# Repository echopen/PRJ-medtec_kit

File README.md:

# Project

## Name
[`PRJ-medtec_kit`]()

## Title @lang=fr
Projet de kit d'expérimentation

## Title @lang=en
Experiment kit project

## About @lang=en
Designing a modular hardware development kit to spread the project and raise contributions.

## Challenge
[`CHG-medtec`]()

## Uses
This repository provid all is needed to make an echOpen kit. It is divided in six folders:  
+ **configurations**, in this folder one find the different working configuration to have a functional kit. It lists the différent daughter board to plug on a mother and the mecanic modules used.  
+ **electronic**, in this folder one can find the daughter boards sources, plans... And to software for the microcontrolers or FPGA.  
+ **installation**, in this folder one can find the instruction to download and install the software need by your computer (linux or windows user). There is also the instructions for installing boards such as arduino or RedPitaya and how to launch the kit.  
+ **license**, in this folder one can find the echOpen license.  
+ **mecanic**, in this folder one can find the sources for mecanic pieces.  
+ **miscellanous** contain informations about functions and interfaces.

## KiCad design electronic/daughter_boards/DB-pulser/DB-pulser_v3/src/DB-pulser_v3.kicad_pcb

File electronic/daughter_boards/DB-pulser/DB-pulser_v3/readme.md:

# Daughter_board

## Name
[`DB-pulser_v2`]()

## Title
Daughter board pulser version 3

## Author
* [`CTC-dubois_jerome`]()

## Modules included
* [`MDL-pulser_v1`]()

## Interfaces
### Input
* [`ITF-A_gnd`]()
* [`ITF-F_12v`]()
* [`ITF-I_pulse_on`]()

### Output
* [`ITF-A_gnd`]()

##External connections
### Input
* -100V (P2, P6)

### Output
* -100V pulse (P4, P5, P7, P8)

## Scheme

## Remarks
[BOM](./src/DB-pulser_v1.csv)

If the cable connecting the transducer to the pulse is too long, one might have loop effect. This can be avoid with impedance adaptation, we are currently working on that.

-100V input is connected to P2 or P6 (angled socket and SMA connector respectively). Connector P4, P5, P7 and P8 are used to plugged the transducer and to connect with DB-tr_switch_tgc.

A small 47 ohms resistors had to be add to have the pulse, it don't work without it.

## Results

## Pros/Cons/Constraint:

**Pros:** cheap solution

**Cons:** NA

**Constraint:** NA

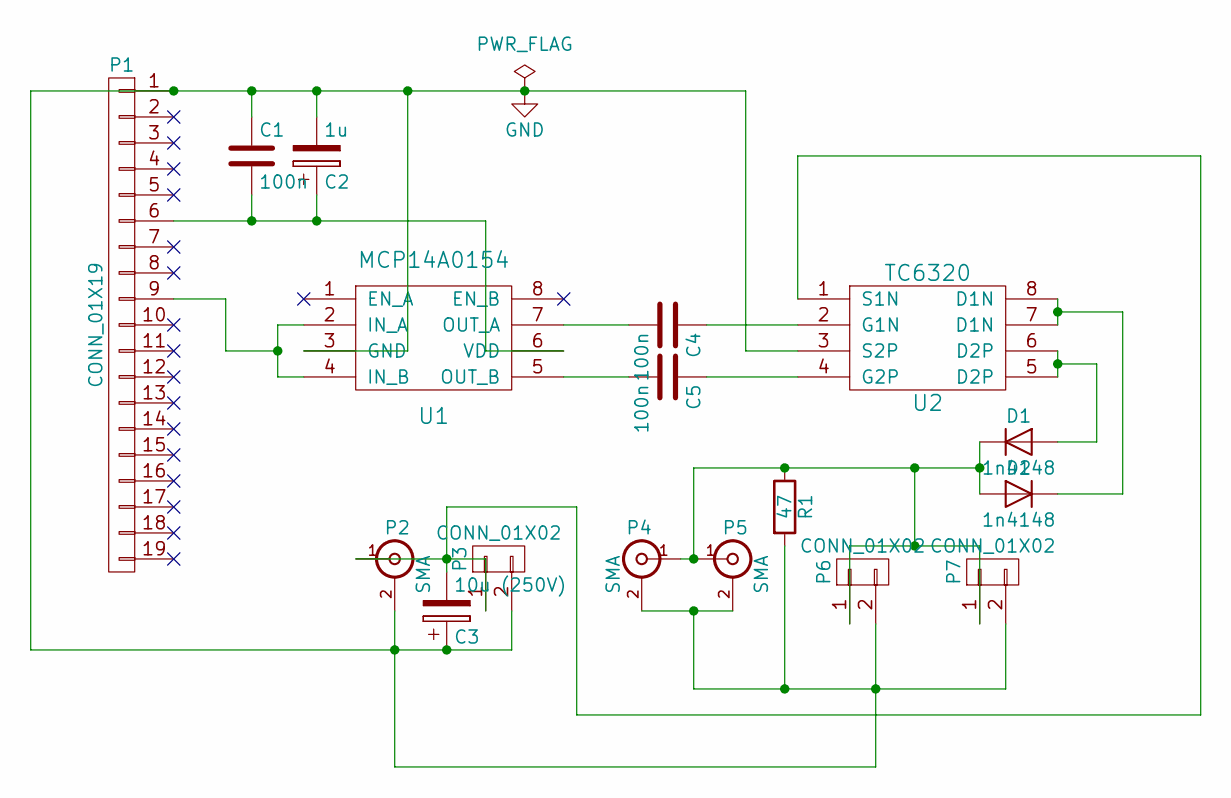
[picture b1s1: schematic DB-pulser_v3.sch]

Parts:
C1, C4, C5: 100n; C_small_TH_echopen
C2: 1u; CP_small_TH_echopen
C3: 10u (250V); CP_small_TH_echopen
D1, D2: 1n4148; D_TH_common
P1: CONN_01X19; Header_pin_angled_1x19
P2, P4, P5: SMA
P3, P6, P7: CONN_01X02; Socket_1x02
R1: 47; Resistor_TH_common
U1: MCP14A0154; MSOP-8
U2: TC6320; SOIC-8

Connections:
GND: C1.1, C2.2, C3.1, P1.1, P2.2 (Ext), P3.2, P4.2 (Ext), P5.2 (Ext), P6.2, P7.2, R1.2, U1.3 (GND), U2.3 (S2P)
unnamed: C1.2, C2.1, P1.6, U1.6 (VDD)
unnamed: C3.2, P2.1 (In), P3.1, U2.1 (S1N)
unnamed: C4.1, U2.2 (G1N)
unnamed: C4.2, U1.7 (OUT_A)
unnamed: C5.1, U2.4 (G2P)
unnamed: C5.2, U1.5 (OUT_B)
unnamed: D1.1 (K), D2.2 (A), P4.1 (In), P5.1 (In), P6.1, P7.1, R1.1
unnamed: D1.2 (A), U2.5 (D2P), U2.6 (D2P)
unnamed: D2.1 (K), U2.7 (D1N), U2.8 (D1N)
unnamed: P1.9, U1.2 (IN_A), U1.4 (IN_B)

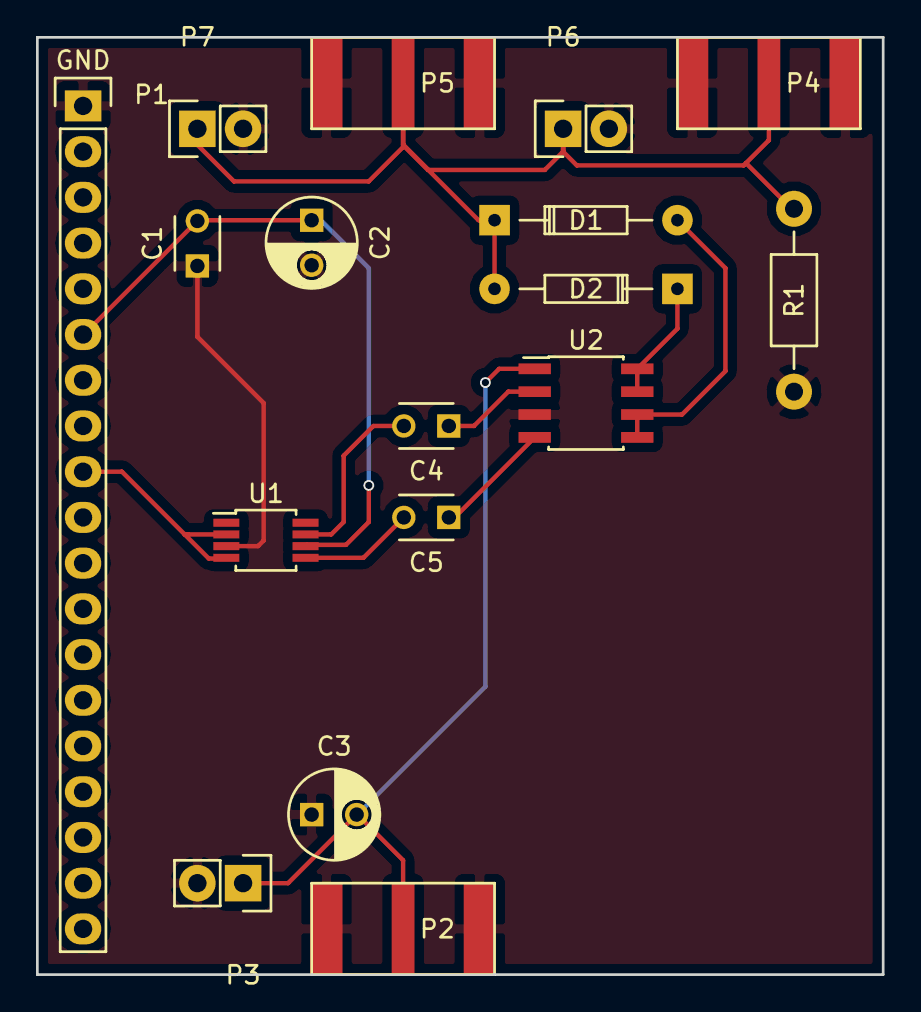
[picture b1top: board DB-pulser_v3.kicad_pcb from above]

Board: 2 copper layers, 47.0 x 52.1 mm, 17 parts (0 on the bottom side), 11 nets.

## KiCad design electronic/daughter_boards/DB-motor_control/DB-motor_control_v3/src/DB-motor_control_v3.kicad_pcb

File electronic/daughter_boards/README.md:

In this repository one can find the different daughter boards of our systeme. Each daughter board can have different version.

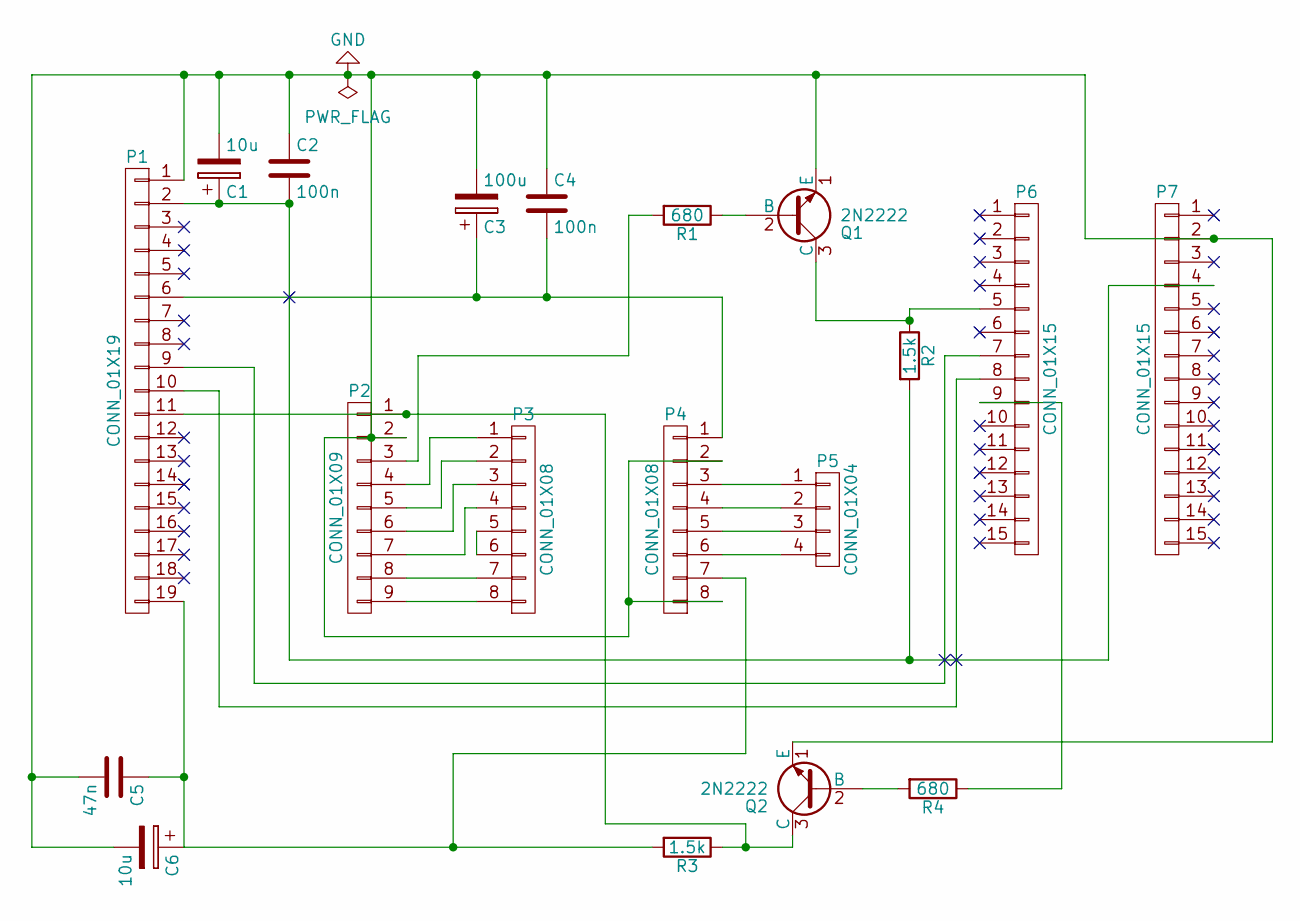
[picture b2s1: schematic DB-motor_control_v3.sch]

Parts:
C1, C6: 10u; CP_small_TH_echopen
C2, C4: 100n; C_small_TH_echopen
C3: 100u; CP_small_TH_echopen
C5: 47n; C_small_TH_echopen
P1: CONN_01X19; Header_pin_angled_1x19
P2: CONN_01X09; Socket_1x09
P3, P4: CONN_01X08; Pin_Header_Straight_1x08
P5: CONN_01X04; Pin_Header_Straight_1x04
P6, P7: CONN_01X15; Pin_Header_Straight_1x15
Q1, Q2: 2N2222; TO-18_TH_common
R1, R4: 680; Resistor_TH_common
R2, R3: 1.5k; Resistor_TH_common

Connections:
GND: C1.2, C2.1, C3.2, C4.1, C5.2, C6.2, P1.1, P2.2, P4.2, P4.8, P7.2, Q1.1 (E), Q2.1 (E)
unnamed: C1.1, C2.2, P1.2, P7.4, R2.2
unnamed: C3.1, C4.2, P1.6, P4.1
unnamed: C5.1, C6.1, P1.19, P4.7, R3.2
unnamed: P1.9, P6.7
unnamed: P1.10, P6.8
unnamed: P1.11, P2.1, Q2.3 (C), R3.1
unnamed: P2.3, R1.2
unnamed: P2.4, P3.1
unnamed: P2.5, P3.2
unnamed: P2.6, P3.3
unnamed: P2.7, P3.4
unnamed: P2.8, P3.7
unnamed: P2.9, P3.8
unnamed: P3.5, P3.6
unnamed: P4.3, P5.1
unnamed: P4.4, P5.2
unnamed: P4.5, P5.3
unnamed: P4.6, P5.4
unnamed: P6.5, Q1.3 (C), R2.1
unnamed: P6.9, R4.1
unnamed: Q1.2 (B), R1.1
unnamed: Q2.2 (B), R4.2

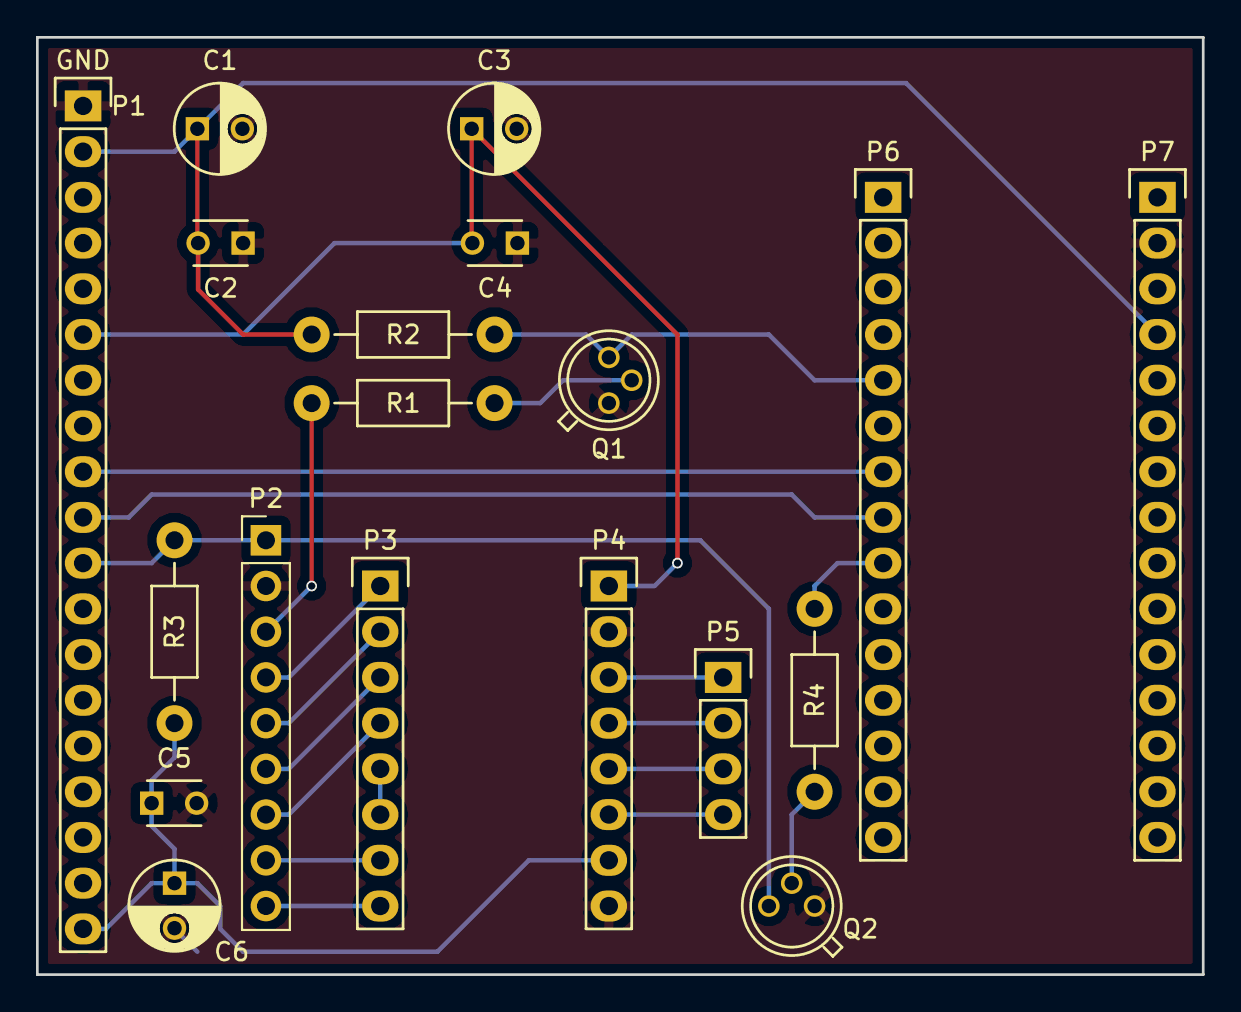
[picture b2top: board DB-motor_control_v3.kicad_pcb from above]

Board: 2 copper layers, 64.8 x 52.1 mm, 19 parts (0 on the bottom side), 23 nets.

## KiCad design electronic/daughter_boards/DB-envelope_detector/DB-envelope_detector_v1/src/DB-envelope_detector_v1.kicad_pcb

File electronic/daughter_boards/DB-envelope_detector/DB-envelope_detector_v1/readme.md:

# Daughter_board

## Name
[`DB-envelope_detector_v1`]()

## Title
Daughter board envelope detector version 1

## Authors
* [`CTC-dubois_jerome`]()

## Modules included
* [`MDL-envelope_detector_v1`](../../../modules/hardware/MDL-envelope_detector/MDL-envelope_detector_v1/readme.md)

## Interfaces
### Input
* [`ITF-A_gnd`]()
* [`ITF-D_amplified_filtered_signal`]()

### Output
* [`ITF-A_gnd`]()
* [`ITF-E_signal_envelope`]()

##External connections
### Input
* NA

### Output
* NA

## Scheme

## Remarks

[BOM](./src/DB-envelope_detector_v1.csv)

## Results

## Pros/Cons/Constraint:

**Pros:** simple

**Cons:** NA

**Constraint:** NA

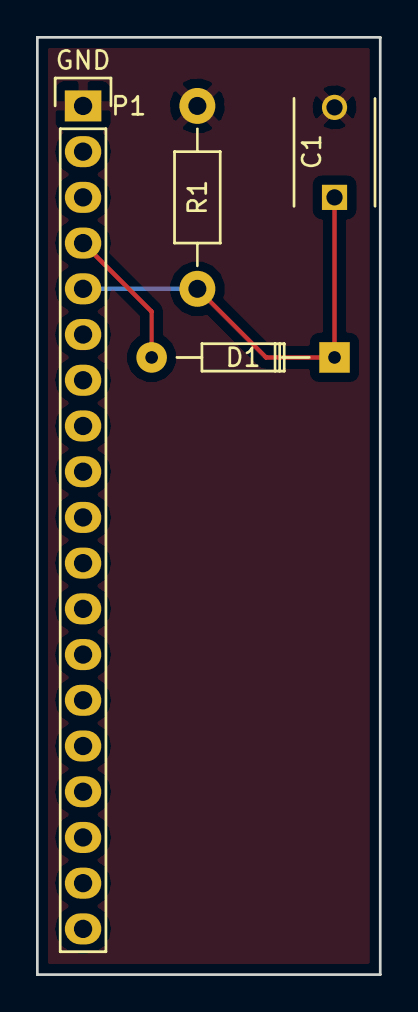
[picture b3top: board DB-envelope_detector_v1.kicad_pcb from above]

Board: 2 copper layers, 19.0 x 52.1 mm, 4 parts (0 on the bottom side), 3 nets.

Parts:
C1: 10p; C_TH_common
D1: 1N60; D_TH_common
P1: CONN_01X19; Header_pin_angled_1x19
R1: 3.9k; Resistor_TH_common

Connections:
GND: C1.2, P1.1, R1.2
unnamed: C1.1, D1.1, P1.5, R1.1
unnamed: D1.2, P1.4

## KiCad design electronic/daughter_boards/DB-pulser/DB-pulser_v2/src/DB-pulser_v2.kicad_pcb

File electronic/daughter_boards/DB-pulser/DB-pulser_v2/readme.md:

# Daughter_board

## Name
[`DB-pulser_v2`]()

## Title
Daughter board pulser version 2

## Author
* [`CTC-dubois_jerome`]()

## Modules included
* [`MDL-pulser_v2`](../../../modules/hardware/MDL-pulser/MDL-pulser_v2/readme.md)

## Interfaces
### Input
* [`ITF-A_gnd`]()
* [`ITF-B_5v`]()
* [`ITF-F_12v`]()
* [`ITF-H_neg_12v`]()
* [`ITF-I_pulse_on`]()

### Output
* [`ITF-A_gnd`]()

##External connections
### Input
* -100V (P2, P4)
* -100V pulse (P3)

### Output
* 5V, +/-12V, -100V, logic pulse
* -100V pulse (P5, P6, P7, P8)

## Scheme

## Remarks
[BOM](./src/DB-pulser_v2.csv)

This daughter board uses an external MAX4940 evaluation kit. This board is connected to the daughter board *via* the connector P3. The -100V input is connected to *via* connector P2 or P4 (angled socket and SMA connector respectively). The output connectors P5, P6, P7, P8 are used to plug the transducer and to connect to `DB_tr_switch_tgc`. 

Scheme on how to connect the MAX4940 to connector P3 is given on [MDL-pulser_v2](../../../modules/hardware/MDL-pulser/MDL-pulser_v2)

## Results

## Pros/Cons/Constraint:

**Pros:** NA

**Cons:** NA

**Constraint:** NA

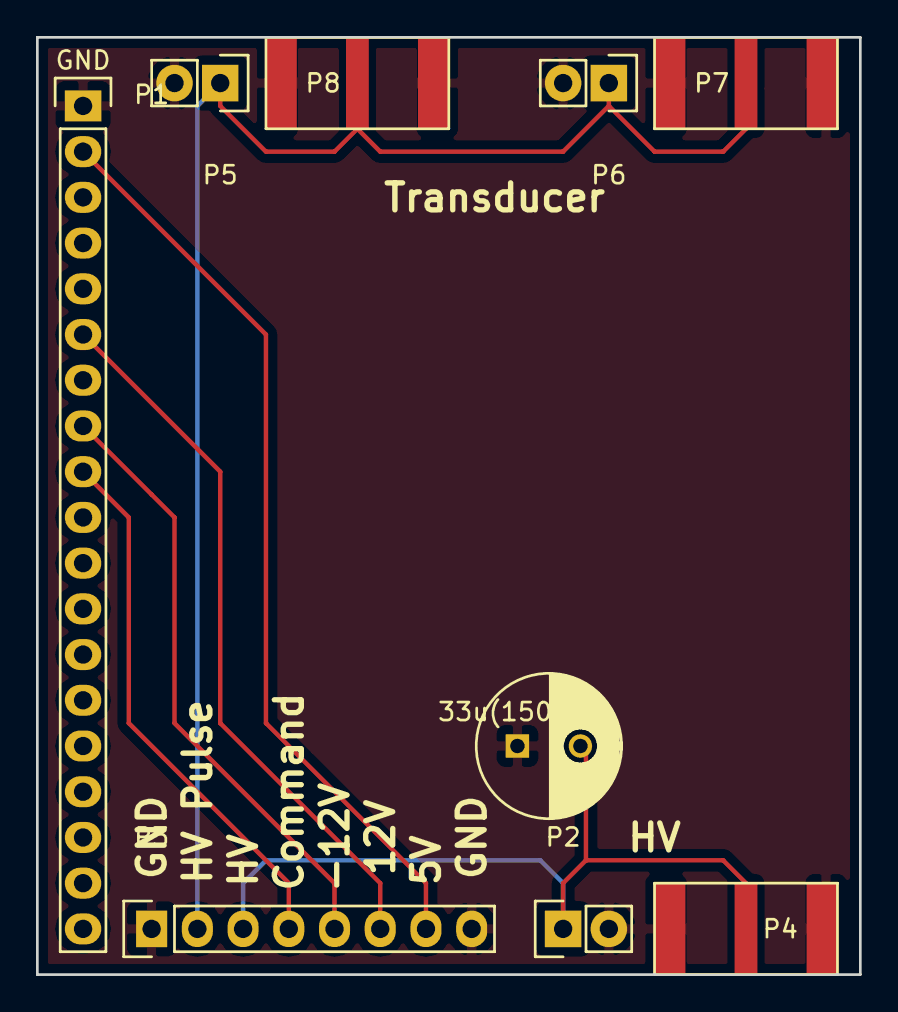
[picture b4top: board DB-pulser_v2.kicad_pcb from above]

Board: 2 copper layers, 45.7 x 52.1 mm, 9 parts (0 on the bottom side), 7 nets.

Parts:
33u(150V)1: CP; CP_TH_common
P1: CONN_01X19; Header_pin_1x19
P2, P5, P6: CONN_01X02; Socket_1x02
P3: CONN_01X08; Socket_Strip_Straight_1x08
P4, P7, P8: SMA

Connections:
GND: 33u(150V)1.1, P1.1, P2.2, P3.1, P3.8, P4.2, P5.2, P6.2, P7.2, P8.2
unnamed: 33u(150V)1.2, P2.1, P3.3, P4.1
unnamed: P1.2, P3.7
unnamed: P1.6, P3.6
unnamed: P1.8, P3.5
unnamed: P1.9, P3.4
unnamed: P3.2, P5.1, P6.1, P7.1, P8.1

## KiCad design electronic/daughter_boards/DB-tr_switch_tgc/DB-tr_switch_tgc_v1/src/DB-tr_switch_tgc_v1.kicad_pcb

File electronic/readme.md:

# Informations

This folder contains the informations and sources to build the electrical parts (daughter boards) of our kit. It is composed of the folders:  
- **daughter_boards**, daughter board informations  
- **miscellianous**, kicad librairy files and datasheets of the electronic parts  
- **modules**, modules informations  

# Uses

If you want to access the informations and the sources a given daughter board juste go in the daughter_board folder (./daughter_board/DVC-) you are interesting in. Open the readme file with a markdown display tool (such as retext) where their is the needed information, the source are accessible simply by clicking on the link.

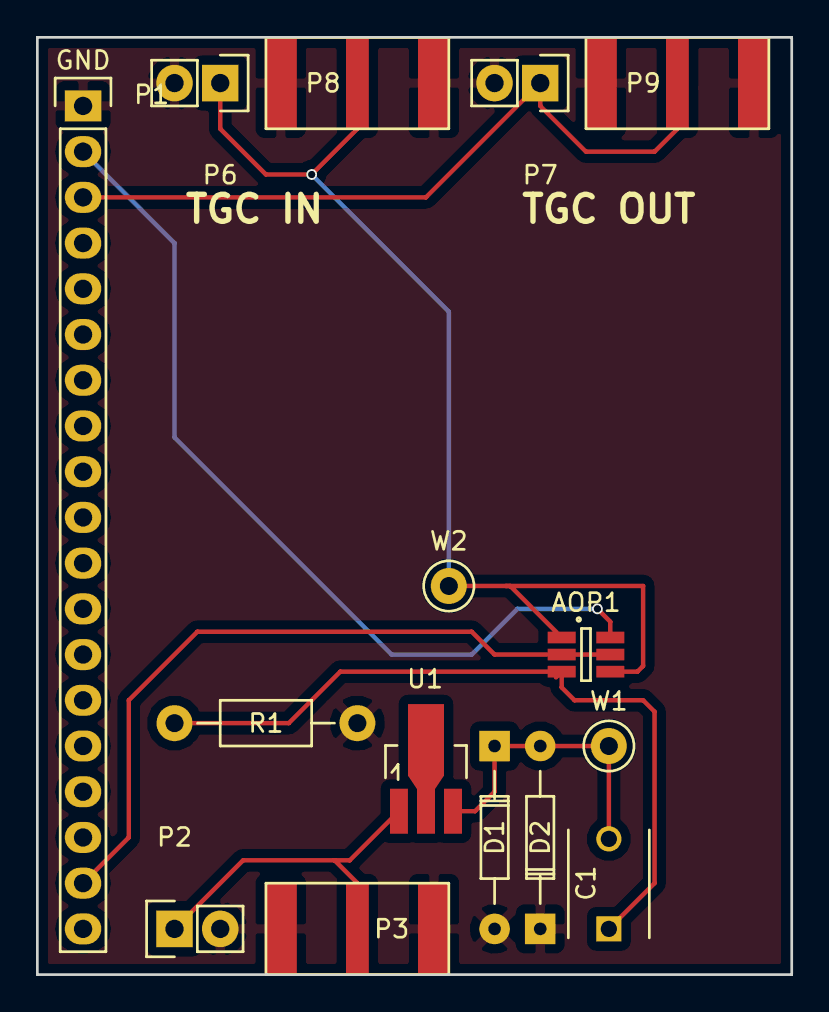
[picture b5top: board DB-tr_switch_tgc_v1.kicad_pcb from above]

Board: 2 copper layers, 41.9 x 52.1 mm, 15 parts (0 on the bottom side), 8 nets.

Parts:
AOP1: OPA625; SOT-23-6_Handsoldering(OPA625)
C1: 1n; C_TH_common
D1, D2: 1N4148; D_TH_common
P1: CONN_01X19; Header_pin_angled_1x19
P2, P6, P7: CONN_01X02; Socket_1x02
P3, P8, P9: SMA
R1: 220; Resistor_TH_common
U1: MD0100; SOT89-3_(MD0100)
W1, W2: TEST_1P; Test_Point

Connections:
GND: D1.2, D2.1, P1.1, P2.2, P3.2, P6.2, P7.2, P8.2, P9.2, R1.2
unnamed: AOP1.1, AOP1.4, P6.1, P8.1, W2.1
unnamed: AOP1.2, AOP1.5, P1.18
unnamed: AOP1.3, C1.1, R1.1
unnamed: AOP1.6, P1.2
unnamed: C1.2, D1.1, D2.2, U1.3, W1.1
unnamed: P1.3, P7.1, P9.1
unnamed: P2.1, P3.1, U1.1

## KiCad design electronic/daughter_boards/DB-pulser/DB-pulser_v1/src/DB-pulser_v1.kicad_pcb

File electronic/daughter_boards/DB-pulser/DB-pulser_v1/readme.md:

# Daughter board

## Name
[`DB-pulser_v1`]()

## Title
Daughter board pulser version 1

## Author
* [`CTC-dubois_jerome`]()

## Modules included
* [`MDL-pulser_v1`]()

## Interfaces
### Input
* [`ITF-A_gnd`]()
* [`ITF-F_12v`]()
* [`ITF-I_pulse_on`]()

### Output
* [`ITF-A_gnd`]()

##External connections
### Input
* -100V (P2, P6)

### Output
* -100V pulse (P4, P5, P7, P8)

## Scheme

## Remarks
[BOM](./src/DB-pulser_v1.csv)

If the cable connecting the transducer to the pulse is too long, one might have loop effect. This can be avoid with impedance adaptation, we are currently working on that.

-100V input is connected to P2 or P6 (angled socket and SMA connector respectively). Connector P4, P5, P7 and P8 are used to plugged the transducer and to connect with DB-tr_switch_tgc.

## Results

## Pros/Cons/Constraint:

**Pros:** NA

**Cons:** NA

**Constraint:** NA

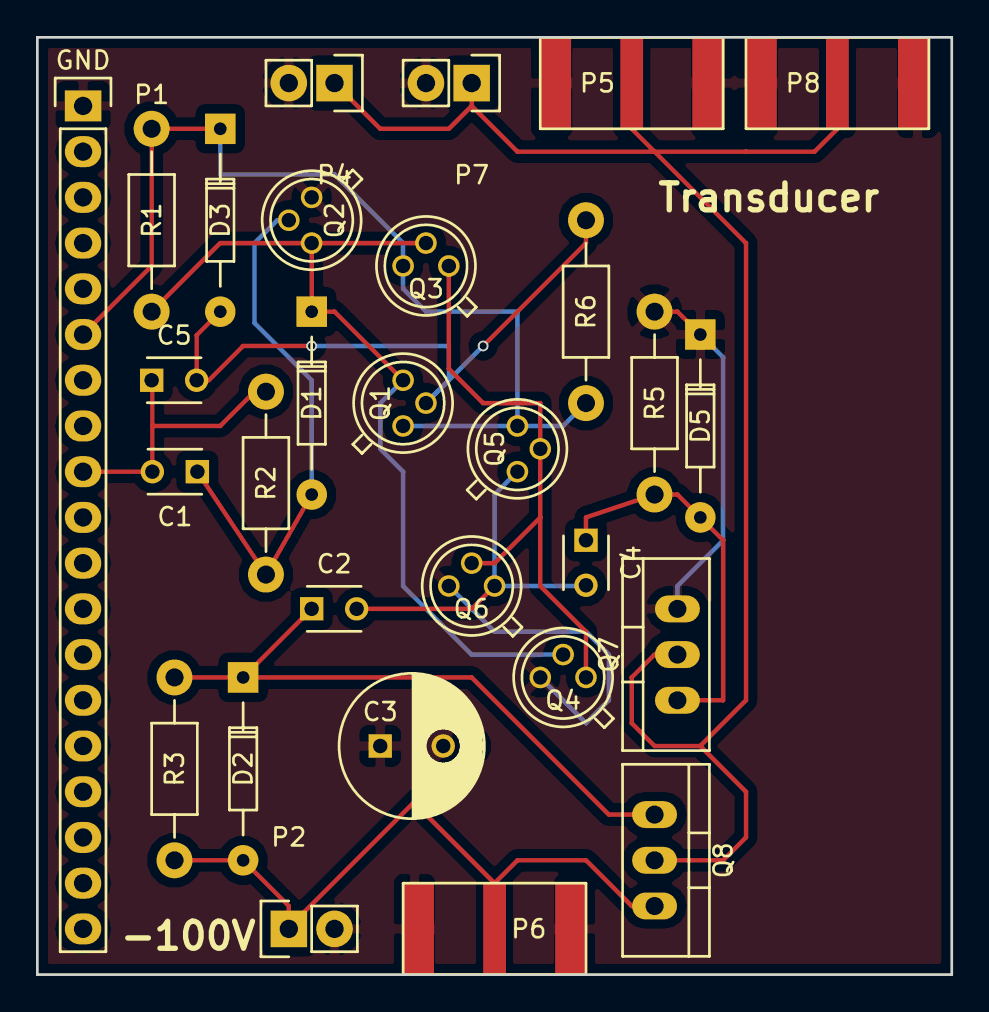
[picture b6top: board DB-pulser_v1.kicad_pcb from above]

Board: 2 copper layers, 50.8 x 52.1 mm, 29 parts (0 on the bottom side), 12 nets.

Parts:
C1: 100p; C_small_TH_echopen
C2, C4: 100n; C_small_TH_echopen
C3: 33u; CP_TH_common
C5: 220p; C_small_TH_echopen
D1: BAT48; D_TH_common
D2, D5: 1N4746; D_TH_common
D3: 1N4148; D_TH_common
P1: CONN_01X19; Header_pin_angled_1x19
P2, P4, P7: CONN_01X02; Socket_1x02
P5, P6, P8: SMA
Q1, Q4, Q6: 2N2907; TO-18_TH_common
Q2, Q3, Q5: 2N2222; TO-18_TH_common
Q7: IRF9610; TO-220_TH_common
Q8: IRF610; TO-220_TH_common
R1: 1k; Resistor_TH_common
R2: 22; Resistor_TH_common
R3, R5: 1M; Resistor_TH_common
R6: 100k; Resistor_TH_common

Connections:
GND: C3.1, D5.1, P1.1, P2.2, P4.2, P5.2, P6.2, P7.2, P8.2, Q2.1, Q4.3, Q6.3, Q7.3, R5.1
unnamed: C1.1, D1.2, Q2.2, R2.1
unnamed: C1.2, C5.1, P1.9, R2.2
unnamed: C2.1, D2.1, Q8.1, R3.1
unnamed: C2.2, C4.2, Q5.1, Q6.1
unnamed: C3.2, D2.2, P2.1, P6.1, Q8.3, R3.2
unnamed: C4.1, D5.2, Q7.1, R5.2
unnamed: C5.2, D3.2, Q1.2, R6.1
unnamed: D1.1, Q1.3, Q2.3, Q3.2, Q4.2, R1.2
unnamed: D3.1, P1.6, Q1.1, Q3.3, Q5.3, R1.1, R6.2
unnamed: P4.1, P5.1, P7.1, P8.1, Q7.2, Q8.2
unnamed: Q3.1, Q4.1, Q5.2, Q6.2

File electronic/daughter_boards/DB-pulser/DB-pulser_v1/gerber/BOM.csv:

Reference, Value, Footprint, Datasheet, Caracteristic, Manufacturer, Ref Manufacturer
R2,22,Echopen:Resistor_TH_common,,1/4W 5%,Yageo,CFR-25JR-52-22R
C1,100p,Echopen:C_TH_common,,25V 10%,Xicon,140-50N5-101J-TB-RC
C5,220p,Echopen:C_TH_common,,25V 10%,Vishay,K221K15X7RF5TL2
D1,BAT48,Echopen:D_TH_common,,NA,STMicroelectronics,BAT48
D3,1N4148,Echopen:D_TH_common,,NA,Fairchild Semiconductor,1N4148
R6,100k,Echopen:Resistor_TH_common,,1/4W 10%,Vishay,CCF07100KJKE36
R1,1k,Echopen:Resistor_TH_common,,1/4W 5%,Yageo,MFR-25FRF52-1K
C2,100n,Echopen:C_TH_common,,25V 20%,Xicon,21RZ310-RC
C4,100n,Echopen:C_TH_common,,25V 20%,Xicon,21RZ310-RC
D5,1N4746,Echopen:D_TH_common,,Zener 18V,Vishay,1N4746A-TR
D2,1N4746,Echopen:D_TH_common,,Zener 18V,Vishay,1N4746A-TR
R5,1M,Echopen:Resistor_TH_common,,1/4W 5%,Yageo,MFR-25FBF52-1M
R3,1M,Echopen:Resistor_TH_common,,1/4W 5%,Yageo,MFR-25FBF52-1M
Q7,IRF9610,Echopen:TO-220_TH_common,,NA,Vishay,IRF9610PBF
Q8,IRF610,Echopen:TO-220_TH_common,,NA,Vishay,IRF610PBF
P1,CONN_01X19,Echopen:Header_pin_angled_1x19,,NA,Molex,22-28-8192
P2,CONN_01X02,Echopen:Socket_1x02,,angled socket 1*02,Molex,22-15-2026
P4,CONN_01X02,Echopen:Socket_1x02,,angled socket 1*02,Molex,22-15-2026
P5,SMA,Echopen:SMA,,NA,Johnson / Cinch Connectivity Solutions,142-0701-801
C3,33u,Echopen:CP_TH_common,,150V 20%,Lelon,REA330M2CBK-1320P
Q1,2N2907,Echopen:TO-18_TH_common,,NA,Central Semiconductor,2N2907A
Q2,2N2222,Echopen:TO-18_TH_common,,NA,Central Semiconductor,2N2222
Q3,2N2222,Echopen:TO-18_TH_common,,NA,Central Semiconductor,2N2222
Q4,2N2907,Echopen:TO-18_TH_common,,NA,Central Semiconductor,2N2907A
Q5,2N2222,Echopen:TO-18_TH_common,,NA,Central Semiconductor,2N2222
Q6,2N2907,Echopen:TO-18_TH_common,,NA,Central Semiconductor,2N2907A
P6,SMA,Echopen:SMA,,NA,Johnson / Cinch Connectivity Solutions,142-0701-801
P7,CONN_01X02,Echopen:Socket_1x02,,angle socket 1*02,Molex,22-15-2026
P8,SMA,Echopen:SMA,,NA,Johnson / Cinch Connectivity Solutions,142-0701-801

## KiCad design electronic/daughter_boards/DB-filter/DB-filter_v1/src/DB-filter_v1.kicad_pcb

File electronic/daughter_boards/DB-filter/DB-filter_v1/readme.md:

# Daughter_board

## Name
[`DB-filter_v1`]()

## Title
Daughter board pass-band filter version 1

## Author
* [`CTC-dubois_jerome`]()

## Modules included
* [`MDL-filter_v1`](../../../modules/hardware/MDL-filter/MDL-filter_v1/readme.md)

## Interfaces
### Input
* [`ITF-A_gnd`]()
* [`ITF-C_amplified_raw_signal`]()

### Output
* [`ITF-A_gnd`]()
* [`ITF-D_amplified_filtered_signal`]()

##External connections
### Input
* NA

### Output
* NA

## Scheme

## Remarks
[BOM](./src/DB-filter_v1.csv)

## Results

## Pros/Cons/Constraint:

**Pros:** simple

**Cons:** NA

**Constraint:** NA

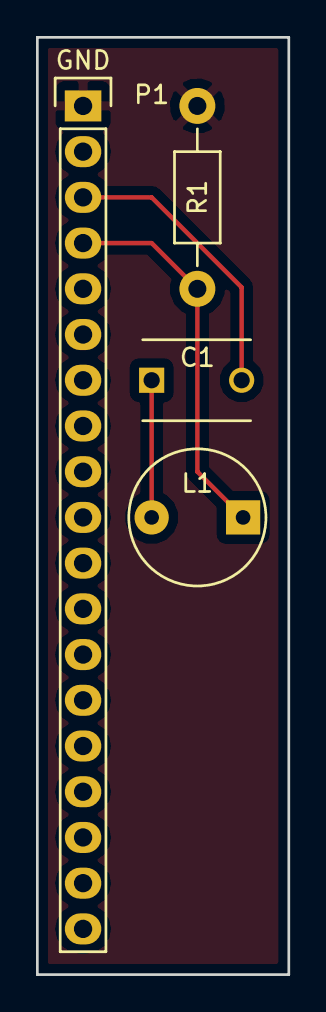
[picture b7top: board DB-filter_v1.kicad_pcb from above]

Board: 2 copper layers, 14.0 x 52.1 mm, 4 parts (0 on the bottom side), 4 nets.

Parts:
C1: 1n; C_TH_common
L1: 10u; INDUCTOR_TH_common
P1: CONN_01X19; Header_pin_angled_1x19
R1: 330; Resistor_TH_common

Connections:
GND: P1.1, R1.2
unnamed: C1.1, L1.2
unnamed: C1.2, P1.3
unnamed: L1.1, P1.4, R1.1

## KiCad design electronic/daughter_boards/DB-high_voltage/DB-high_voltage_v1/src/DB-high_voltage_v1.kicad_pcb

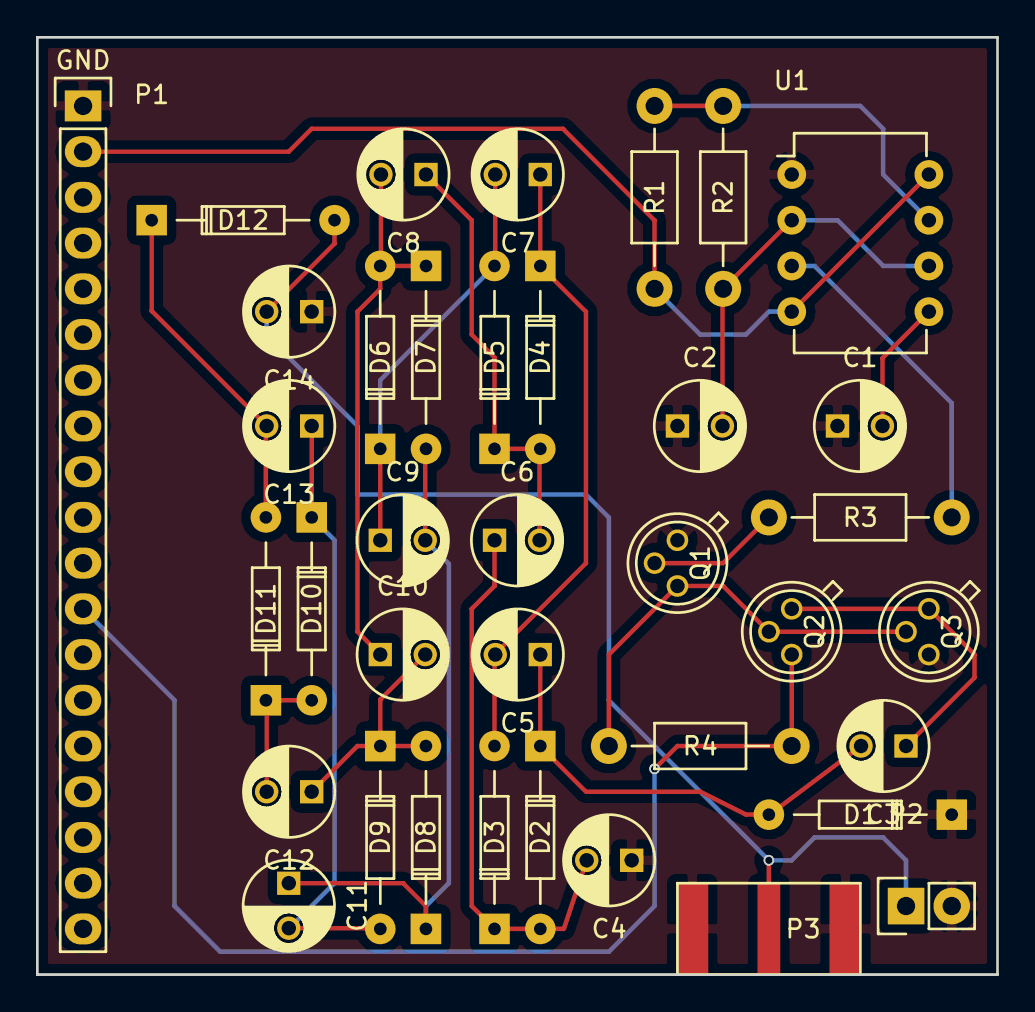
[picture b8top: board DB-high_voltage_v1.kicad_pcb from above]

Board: 2 copper layers, 53.3 x 52.1 mm, 37 parts (0 on the bottom side), 22 nets.

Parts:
C1: 10n; CP_small_TH_echopen
C2: 47n; CP_small_TH_echopen
C3: 47u; CP_small_TH_echopen
C4, C5, C6, C7, C8, C9, C10, C11, C12, C13, C14: 4.7u; CP_small_TH_echopen
D1, D2, D3, D4, D5, D6, D7, D8, D9, D10, D11, D12: 1N4148; D_TH_common
P1: CONN_01X19; Header_pin_angled_1x19
P2: CONN_01X02; Socket_1x02
P3: SMA
Q1, Q2: 2N2222; TO-18_TH_common
Q3: 2N2907; TO-18_TH_common
R1: 2.2k; Resistor_TH_common
R2: 12k; Resistor_TH_common
R3: 3.3k; Resistor_TH_common
R4: 1.8k; Resistor_TH_common
U1: LM555N; DIP-8(LM555)

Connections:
GND: C1.1, C2.1, C4.1, C14.1, D1.1, P1.1, P2.2, P3.2, Q1.1, Q3.3, U1.1
unnamed: C1.2, U1.5
unnamed: C2.2, R2.2, U1.2, U1.6
unnamed: C3.1, Q2.1, Q3.1
unnamed: C3.2, C5.1, D1.2, D2.1
unnamed: C4.2, C6.1, D2.2, D3.1
unnamed: C5.2, C7.1, D3.2, D4.1
unnamed: C6.2, C8.1, D4.2, D5.1
unnamed: C7.2, C9.1, D5.2, D6.1
unnamed: C8.2, C10.1, D6.2, D7.1
unnamed: C10.2, C12.1, D8.2, D9.1
unnamed: C9.2, C11.1, D7.2, D8.1
unnamed: C11.2, C13.1, D9.2, D10.1
unnamed: C12.2, D10.2, D11.1
unnamed: C13.2, D11.2, D12.1
unnamed: C14.2, D12.2, P2.1, P3.1
unnamed: P1.12, Q2.3, R4.1
unnamed: Q1.2, R3.1
unnamed: Q1.3, Q2.2, Q3.2, R4.2
unnamed: R1.1, R2.1, U1.7
unnamed: R3.2, U1.3
VCC: P1.2, R1.2, U1.4, U1.8

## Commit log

2016-10-06 Update file structure
2016-10-07 Adding echOpen licence
2016-10-07 Update with licence creation date
2016-10-07 Add pdf echopen_general_public_licence_20150915
2016-10-07 testing module documentation
2016-10-07 Un cr manquant
2016-10-14 Update file structure, work in progress !
2016-10-27 update modules repo
2016-11-01 update modules
2016-11-03 update modules and daughter boards
2016-11-04 Problem with ":" in filename on Windows
2016-11-04 Remove filename with accents
2016-11-04 update documentation
2016-11-05 update daughter boards documentation
2016-11-06 Typo
2016-11-08 installation files for windows and linux
2016-11-08 update installation files
2016-11-09 update installation repo and clean
2016-11-09 reworking repos
2016-11-10 deleting double files
2016-11-13 Error in contact names correction
2016-11-14 Typos
2016-11-15 Rename last version of the kit
2016-11-17 Modify image generation
2016-11-18 correcting .ino
2016-11-18 broken link
2016-11-20 Replacing ambiguous title "Description" with "About" which imply a shorter description paragraph.
2016-11-25 Oop's
2016-11-26 Add some authors
2016-12-02 update src of DBs
2016-12-19 Adding some ICs modules
2016-12-19 Adding the CFG-arduino_servo
2016-12-19 Fixing modules link
2016-12-19 Last bits of cleaning
2016-12-21 adding motor_control_v3
2017-01-02 Correcting some links
2017-01-24 adding motor_control_v3 and trs_tgc_v2
2017-02-21 adding new pulser board
2017-03-07 update pulser ref
2017-04-07 sorting codes
2017-04-07 correct MDL pulser and update DB motor control
2017-04-10 cleaning repos
2017-04-11 corrections
2017-04-12 adding motor_control_v3 documentation
2017-04-14 adding cfg-aquarium
2017-04-18 update documentation and codes
2017-05-10 correcting code
2017-05-19 adding MDL uc_v3
2017-05-19 update config
2017-05-24 Add doc builder script
2017-05-24 Typos in readme.md and file names.
2017-05-24 Documentation static web site regenerated.
2017-05-30 Correcting some typos
2017-07-12 update DB-motor_control_v3
2017-07-12 update DB-motor_control_v3 2
2017-12-18 update instalation doc
2017-12-18 update instalation doc2
2017-12-18 update instalation doc3
2017-12-19 update instalation doc4
